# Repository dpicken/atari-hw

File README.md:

# atari-hw

Atari 8-bit hardware projects.

- [Small Form Factor (SFF) Atari 8-bit compatible system](/doc/sbc.md)

- [USB Keyboard Controller for Atari XL/XE computers](/doc/keyboard-usb-qtpy.md)

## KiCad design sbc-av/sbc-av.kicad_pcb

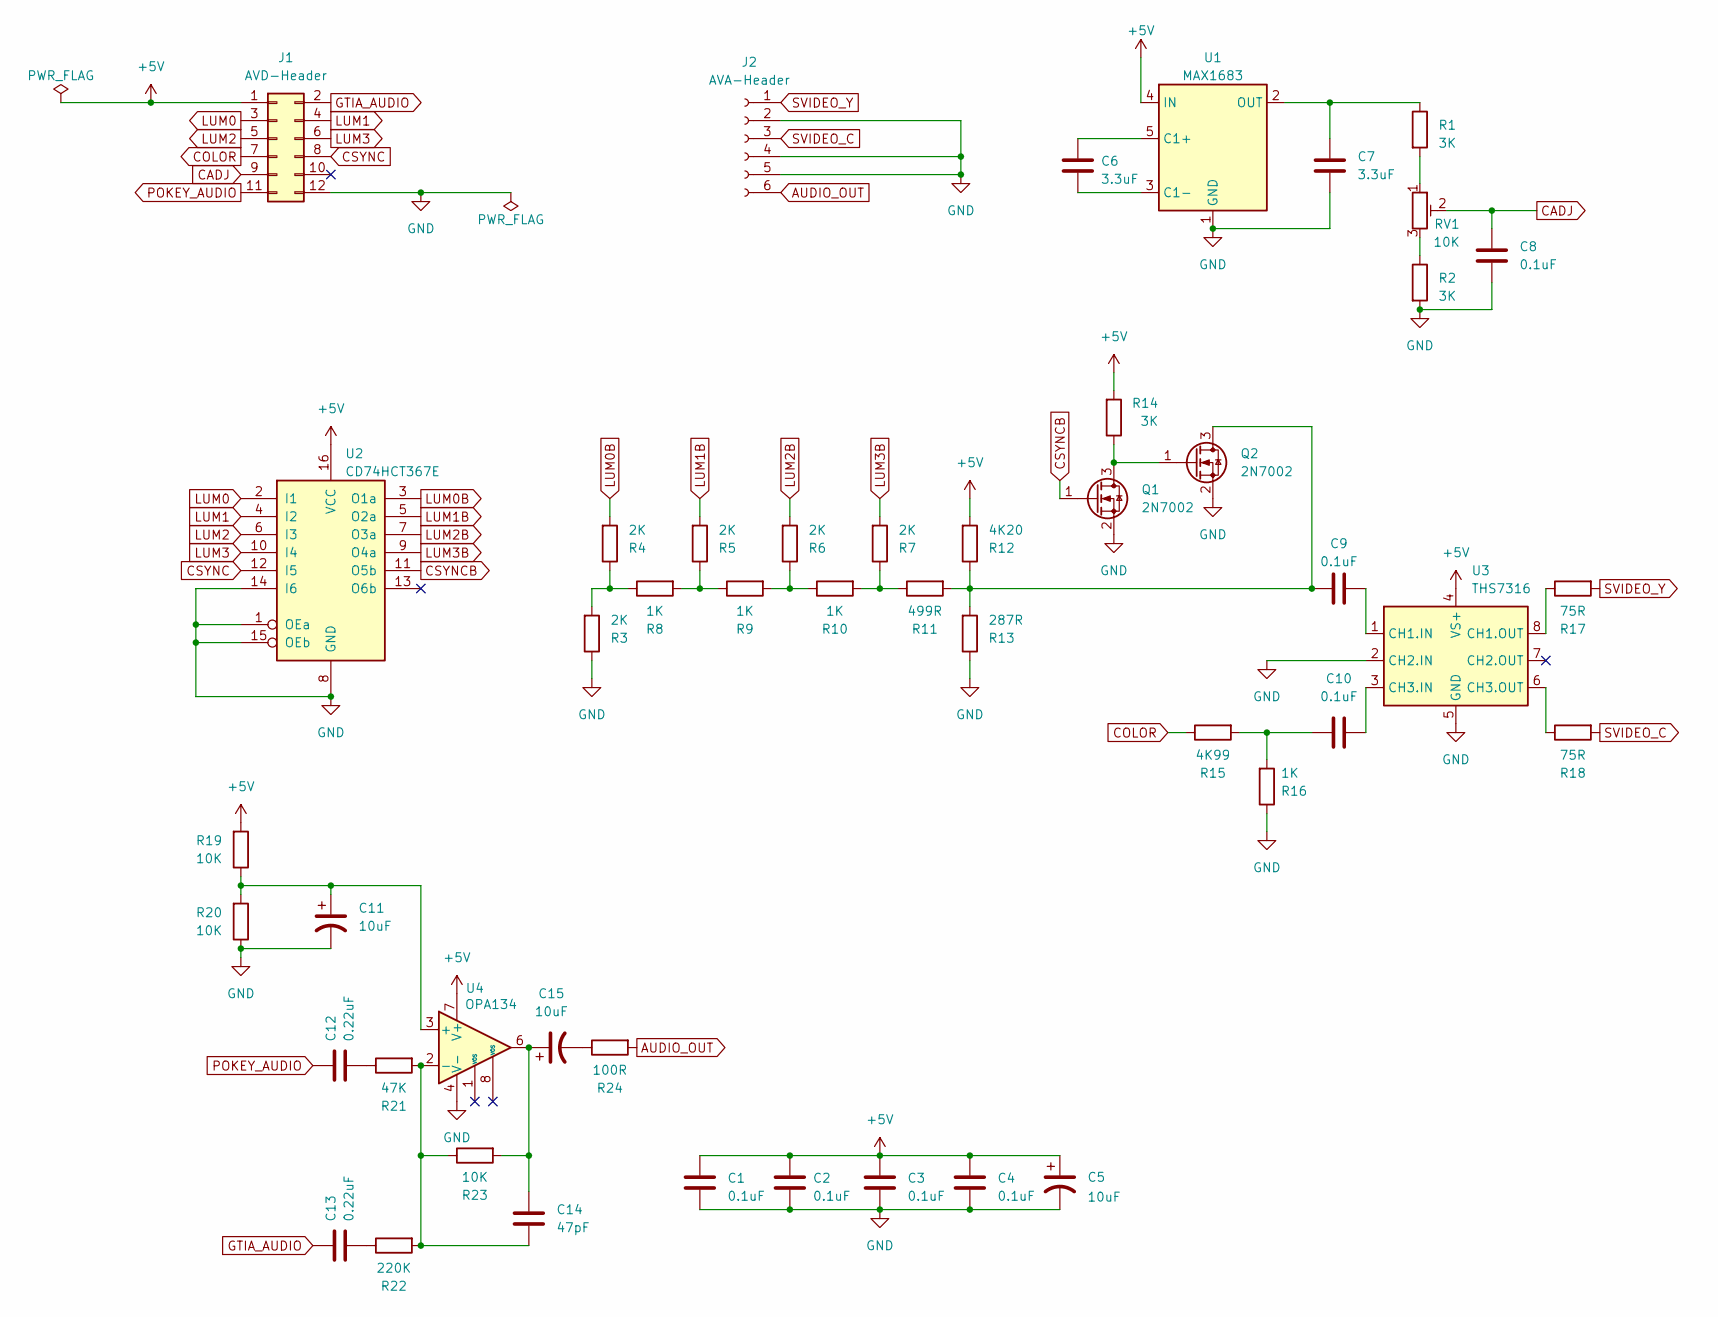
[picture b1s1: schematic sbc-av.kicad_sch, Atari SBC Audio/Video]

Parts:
C1, C2, C3, C4, C8, C9, C10: 0.1uF; C_0805_2012Metric_Pad1.18x1.45mm_HandSolder
C5, C11: 10uF; CP_EIA-2012-15_AVX-P_HandSolder
C6, C7: 3.3uF; C_0805_2012Metric_Pad1.18x1.45mm_HandSolder
C12, C13: 0.22uF; C_1206_3216Metric_Pad1.33x1.80mm_HandSolder
C14: 47pF; C_0805_2012Metric_Pad1.18x1.45mm_HandSolder
C15: 10uF; CP_EIA-3216-18_Kemet-A_HandSolder
J1: AVD-Header; PinHeader_2x06_P2.54mm_Vertical
J2: AVA-Header; PinHeader_1x06_P2.54mm_Vertical
Q1, Q2: 2N7002; SOT-23
R1, R2, R14: 3K; R_0805_2012Metric_Pad1.20x1.40mm_HandSolder
R3, R4, R5, R6, R7: 2K; R_0805_2012Metric_Pad1.20x1.40mm_HandSolder
R8, R9, R10, R16: 1K; R_0805_2012Metric_Pad1.20x1.40mm_HandSolder
R11: 499R; R_0805_2012Metric_Pad1.20x1.40mm_HandSolder
R12: 4K20; R_0805_2012Metric_Pad1.20x1.40mm_HandSolder
R13: 287R; R_0805_2012Metric_Pad1.20x1.40mm_HandSolder
R15: 4K99; R_0805_2012Metric_Pad1.20x1.40mm_HandSolder
R17, R18: 75R; R_0805_2012Metric_Pad1.20x1.40mm_HandSolder
R19, R20, R23: 10K; R_0805_2012Metric_Pad1.20x1.40mm_HandSolder
R21: 47K; R_0805_2012Metric_Pad1.20x1.40mm_HandSolder
R22: 220K; R_0805_2012Metric_Pad1.20x1.40mm_HandSolder
R24: 100R; R_0805_2012Metric_Pad1.20x1.40mm_HandSolder
RV1: 10K; Potentiometer_Bourns_3314G_Vertical
U1: MAX1683; SOT-23-5
U2: CD74HCT367E; SOIC-16_3.9x9.9mm_P1.27mm
U3: THS7316; SOIC-8_3.9x4.9mm_P1.27mm
U4: OPA134; SOIC-8_3.9x4.9mm_P1.27mm

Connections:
+5V: C1.1, C2.1, C3.1, C4.1, C5.1, J1.1, R12.2, R14.2, R19.2, U1.4 (IN), U2.16 (VCC), U3.4 (VS+), U4.7 (V+)
AUDIO_OUT: J2.6, R24.2
CADJ: C8.1, J1.9, RV1.2
COLOR: J1.7, R15.1
CSYNC: J1.8, U2.12 (I5)
CSYNCB: Q1.1 (G), U2.11 (O5b)
GND: C1.2, C2.2, C3.2, C4.2, C5.2, C7.2, C8.2, C11.2, J1.12, J2.2, J2.4, J2.5, Q1.2 (S), Q2.2 (S), R2.2, R3.1, R13.1, R16.1, R20.1, U1.1 (GND), U2.1 (OEa), U2.8 (GND), U2.14 (I6), U2.15 (OEb), U3.2 (CH2.IN), U3.5 (GND), U4.4 (V-)
GTIA_AUDIO: C13.1, J1.2
LUM0: J1.3, U2.2 (I1)
LUM0B: R4.2, U2.3 (O1a)
LUM1: J1.4, U2.4 (I2)
LUM1B: R5.2, U2.5 (O2a)
LUM2: J1.5, U2.6 (I3)
LUM2B: R6.2, U2.7 (O3a)
LUM3: J1.6, U2.10 (I4)
LUM3B: R7.2, U2.9 (O4a)
unnamed: C10.1, R15.2, R16.2
unnamed: C12.2, R21.1
unnamed: C13.2, R22.1
unnamed: C14.2, C15.1, R23.2, U4.6
unnamed: C15.2, R24.1
unnamed: Q1.3 (D), Q2.1 (G), R14.1
unnamed: C9.1, Q2.3 (D), R11.2, R12.1, R13.2
unnamed: R1.2, RV1.1
unnamed: R2.1, RV1.3
unnamed: R3.2, R4.1, R8.1
unnamed: R5.1, R8.2, R9.1
unnamed: R6.1, R9.2, R10.1
unnamed: R7.1, R10.2, R11.1
unnamed: C6.1, U1.5 (C1+)
unnamed: C6.2, U1.3 (C1-)
unnamed: C7.1, R1.1, U1.2 (OUT)
unnamed: C9.2, U3.1 (CH1.IN)
unnamed: R17.1, U3.8 (CH1.OUT)
unnamed: C10.2, U3.3 (CH3.IN)
unnamed: R18.1, U3.6 (CH3.OUT)
unnamed: C11.1, R19.1, R20.2, U4.3 (+)
unnamed: C14.1, R21.2, R22.2, R23.1, U4.2 (-)
POKEY_AUDIO: C12.1, J1.11
SVIDEO_C: J2.3, R18.2
SVIDEO_Y: J2.1, R17.2

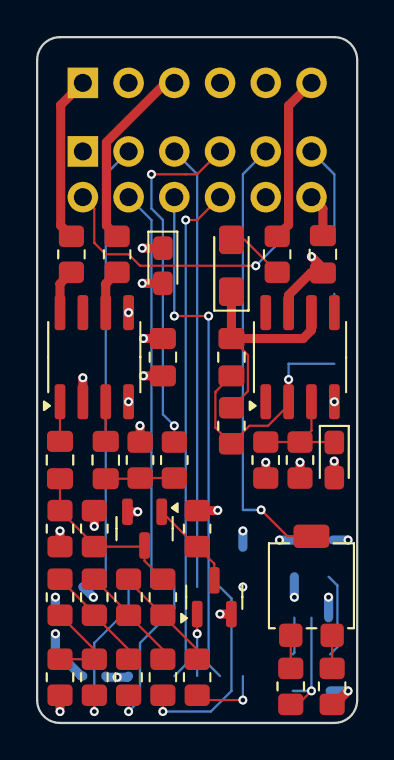
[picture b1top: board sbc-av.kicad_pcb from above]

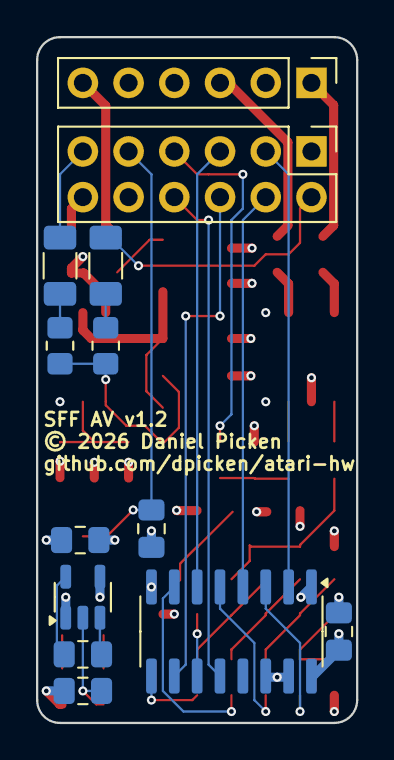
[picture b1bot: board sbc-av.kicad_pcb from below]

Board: 4 copper layers, 17.8 x 38.1 mm, 48 parts (13 on the bottom side), 41 nets.

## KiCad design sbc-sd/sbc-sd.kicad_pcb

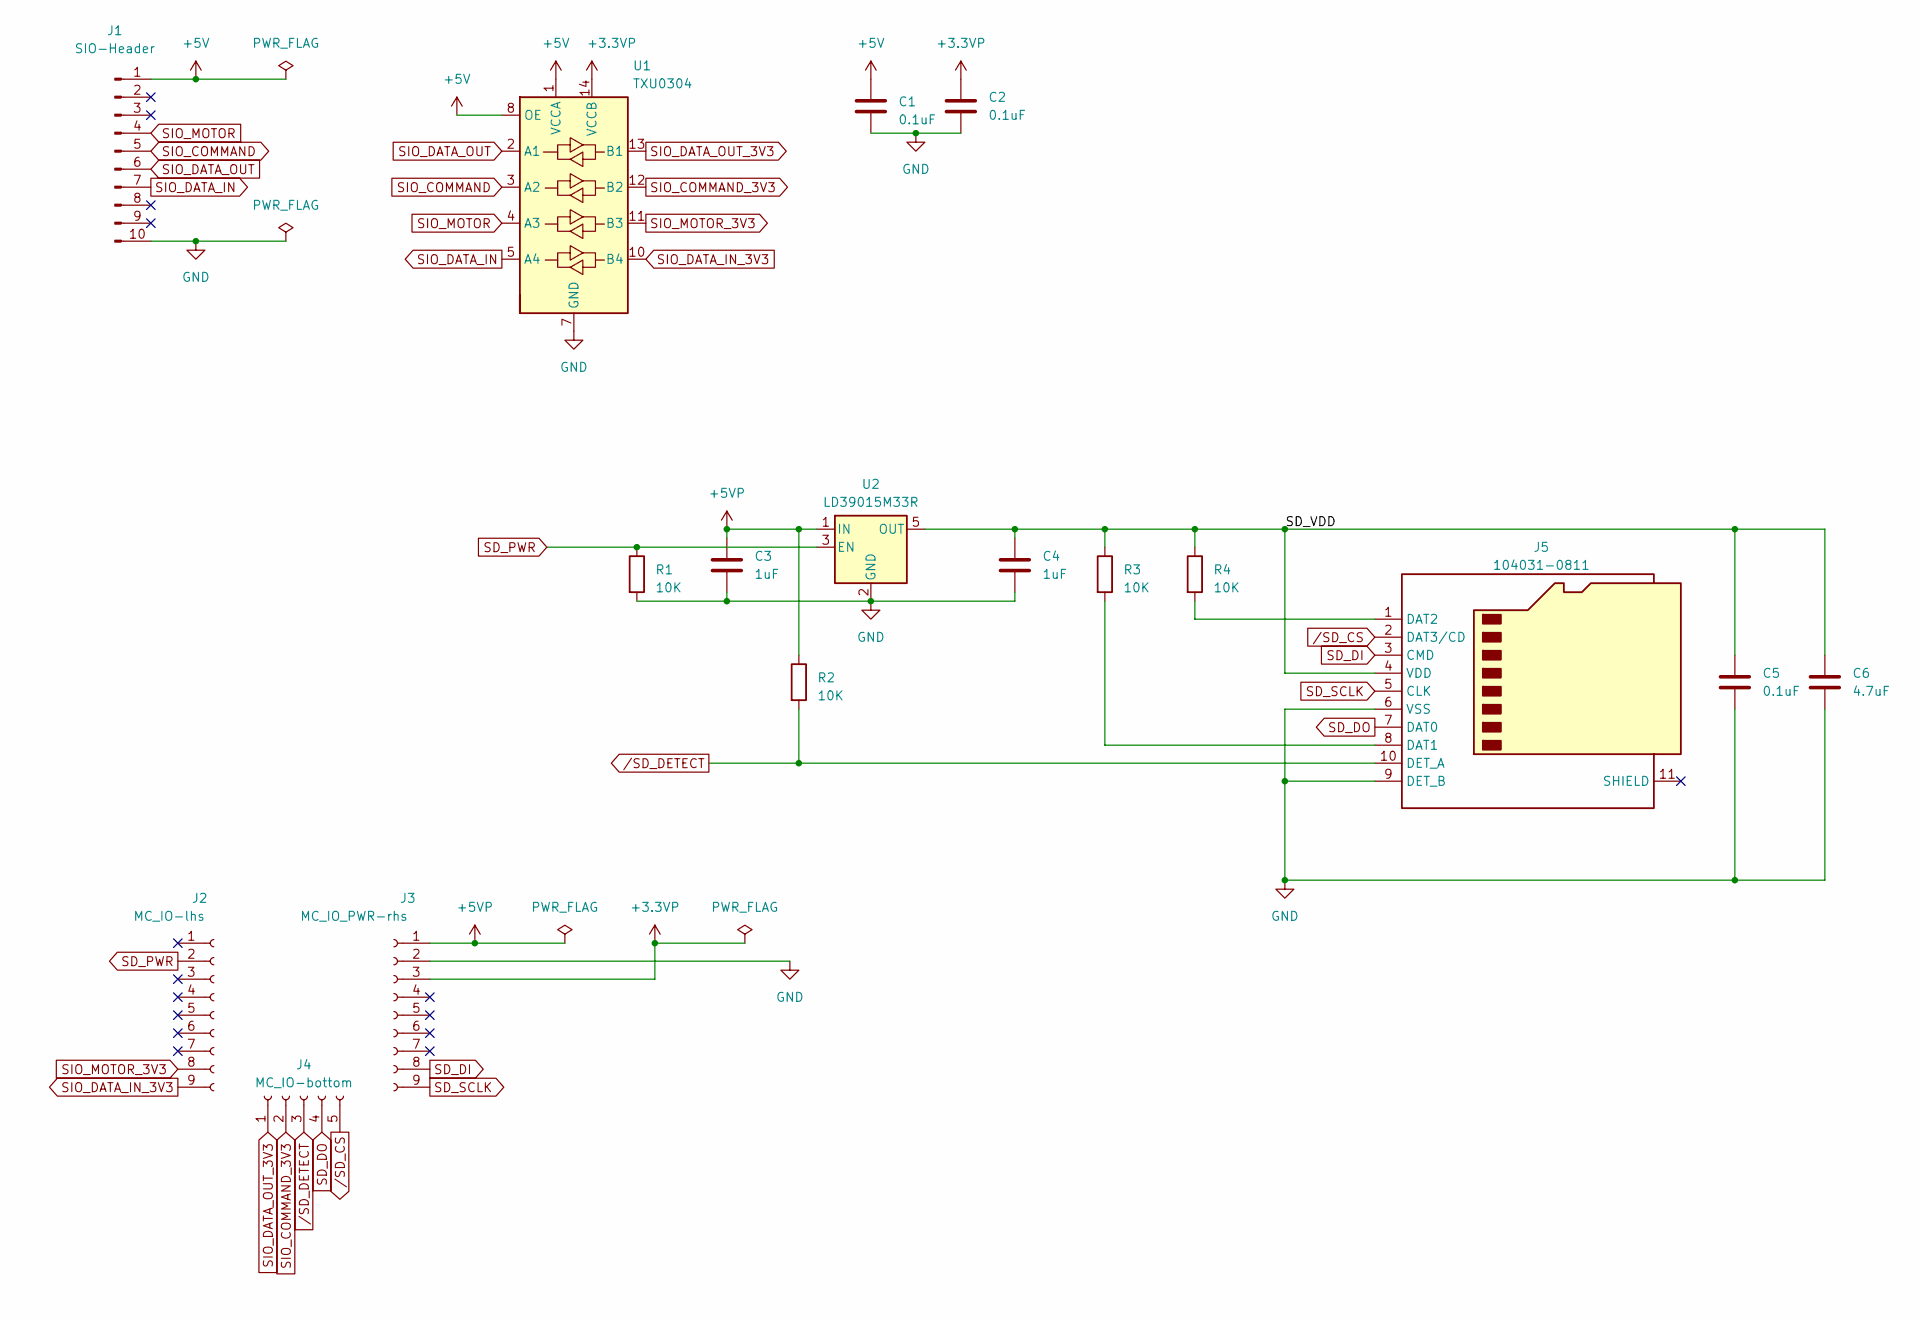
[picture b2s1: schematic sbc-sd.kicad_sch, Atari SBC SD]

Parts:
C1, C2, C5: 0.1uF; C_0805_2012Metric_Pad1.18x1.45mm_HandSolder
C3, C4: 1uF; C_0805_2012Metric_Pad1.18x1.45mm_HandSolder
C6: 4.7uF; C_0805_2012Metric_Pad1.18x1.45mm_HandSolder
J1: SIO-Header; PinHeader_1x10_P2.54mm_Vertical
J2: MC_IO-lhs; PinHeader_1x09_P2.54mm_Vertical
J3: MC_IO_PWR-rhs; PinHeader_1x09_P2.54mm_Vertical
J4: MC_IO-bottom; PinHeader_1x05_P2.54mm_Vertical
J5: 104031-0811; microSD_HC_Molex_104031-0811
R1, R2, R3, R4: 10K; R_0805_2012Metric_Pad1.20x1.40mm_HandSolder
U1: TXU0304; TSSOP-14_4.4x5mm_P0.65mm
U2: LD39015M33R; SOT-23-5

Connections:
+3.3VP: C2.1, J3.3, U1.14 (VCCB)
+5V: C1.1, J1.1, U1.1 (VCCA), U1.8 (OE)
+5VP: C3.1, J3.1, R2.1, U2.1 (IN)
/SD_VDD: C4.1, C5.1, C6.1, J5.4 (VDD), R3.1, R4.1, U2.5 (OUT)
GND: C1.2, C2.2, C3.2, C4.2, C5.2, C6.2, J1.10, J3.2, J5.6 (VSS), J5.9 (DET_B), R1.2, U1.7 (GND), U2.2 (GND)
unnamed: J5.8 (DAT1), R3.2
unnamed: J5.1 (DAT2), R4.2
SD_DI: J3.8, J5.3 (CMD)
SD_DO: J4.4, J5.7 (DAT0)
SD_PWR: J2.2, R1.1, U2.3 (EN)
SD_SCLK: J3.9, J5.5 (CLK)
SIO_COMMAND: J1.5, U1.3 (A2)
SIO_COMMAND_3V3: J4.2, U1.12 (B2)
SIO_DATA_IN: J1.7, U1.5 (A4)
SIO_DATA_IN_3V3: J2.9, U1.10 (B4)
SIO_DATA_OUT: J1.6, U1.2 (A1)
SIO_DATA_OUT_3V3: J4.1, U1.13 (B1)
SIO_MOTOR: J1.4, U1.4 (A3)
SIO_MOTOR_3V3: J2.8, U1.11 (B3)
/SD_CS: J4.5, J5.2 (DAT3/CD)
/SD_DETECT: J4.3, J5.10 (DET_A), R2.2

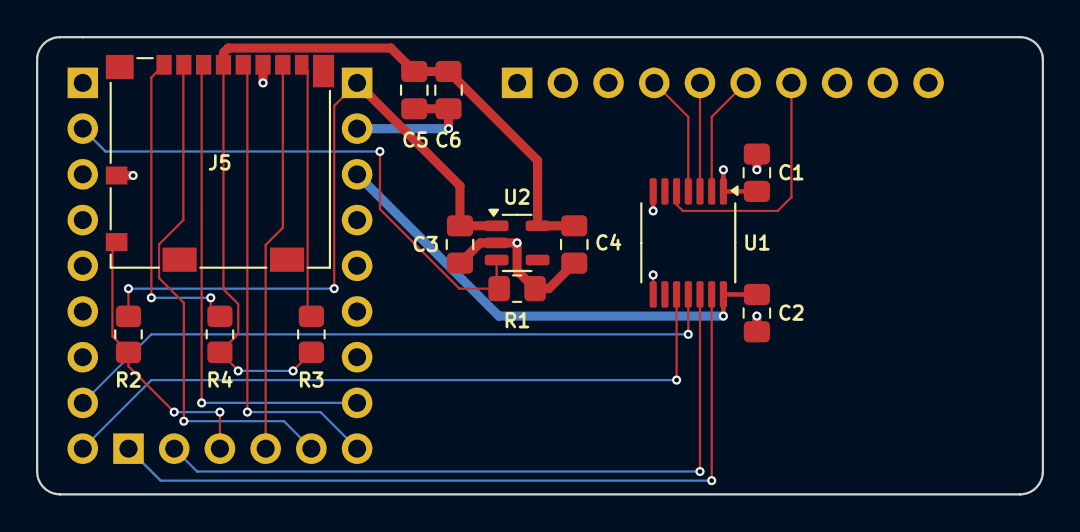
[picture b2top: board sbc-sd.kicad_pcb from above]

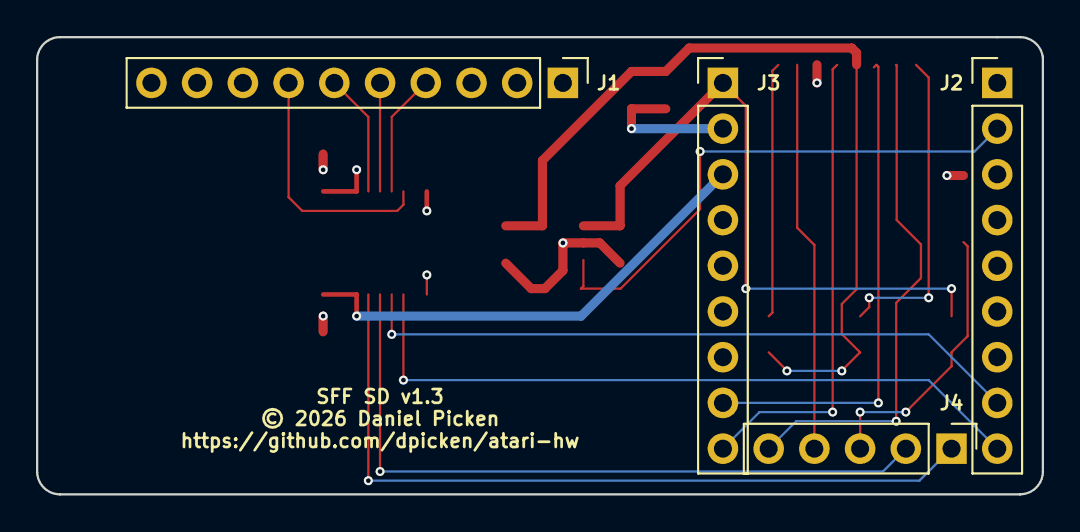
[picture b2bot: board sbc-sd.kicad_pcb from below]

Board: 4 copper layers, 55.9 x 25.4 mm, 17 parts (4 on the bottom side), 21 nets.

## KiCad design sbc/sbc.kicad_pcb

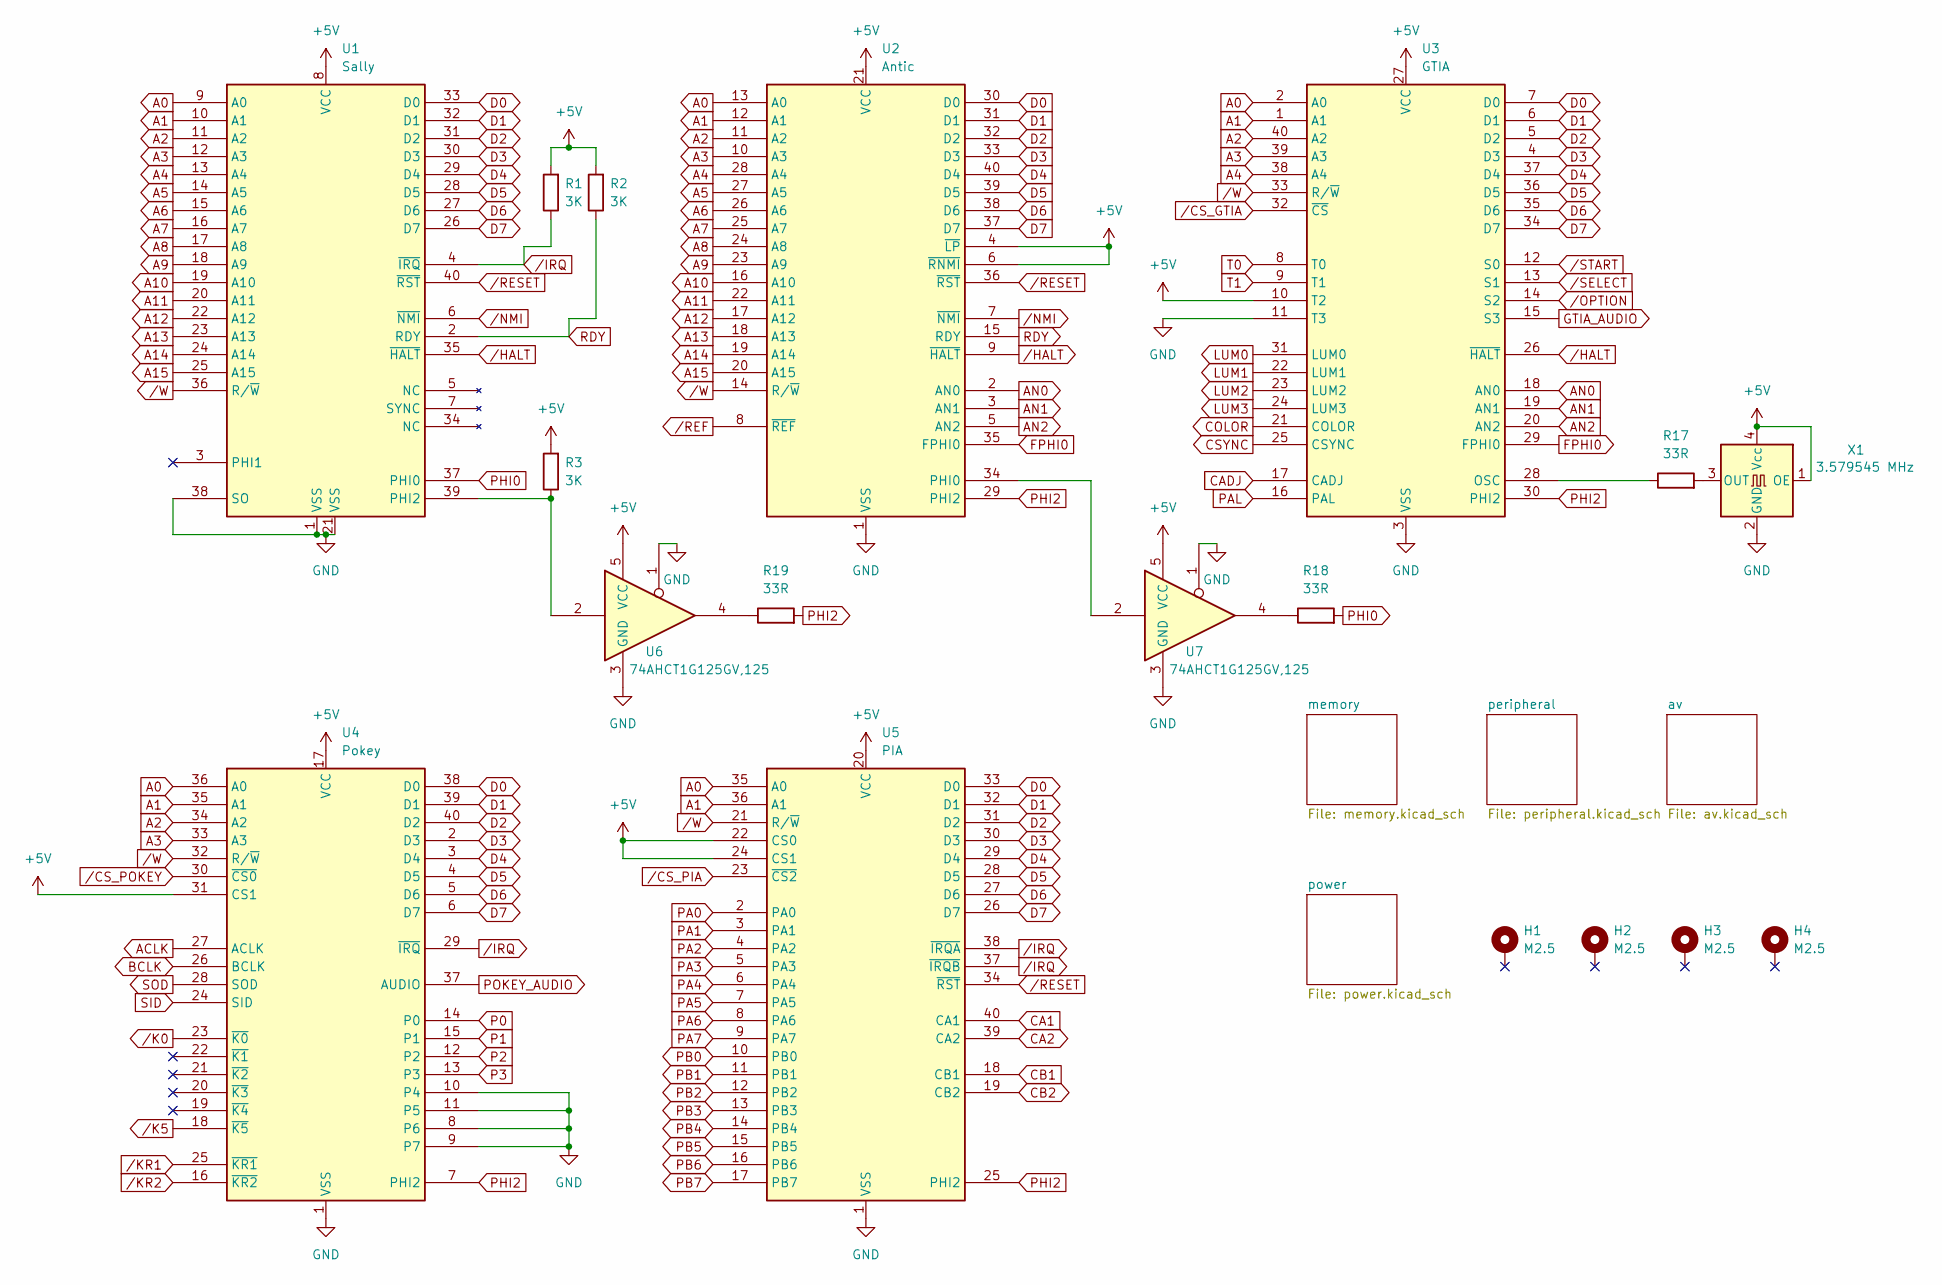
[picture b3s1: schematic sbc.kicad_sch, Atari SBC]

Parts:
H1, H2, H3, H4: M2.5; MountingHole_2.7mm_M2.5_Pad
R1, R2, R3: 3K; R_0805_2012Metric_Pad1.20x1.40mm_HandSolder
R17, R18, R19: 33R; R_0805_2012Metric_Pad1.20x1.40mm_HandSolder
U1: Sally; DIP-40_W15.24mm_Socket
U2: Antic; DIP-40_W15.24mm_Socket
U3: GTIA; DIP-40_W15.24mm_Socket
U4: Pokey; DIP-40_W15.24mm_Socket
U5: PIA; DIP-40_W15.24mm_Socket
U6, U7: 74AHCT1G125GV,125; SOT-23-5_HandSoldering
X1: 3.579545 MHz; Oscillator_SMD_SeikoEpson_SG8002CA-4Pin_7.0x5.0mm

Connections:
+5V: R1.2, R2.2, R3.2, U1.8 (VCC), U2.4 (~LP), U2.6 (~RNMI), U2.21 (VCC), U3.10 (T2), U3.27 (VCC), U4.17 (VCC), U4.31 (CS1), U5.20 (VCC), U5.22 (CS0), U5.24 (CS1), U6.5 (VCC), U7.5 (VCC), X1.1 (OE), X1.4 (Vcc); also elsewhere on the board
A0: U1.9 (A0), U2.13 (A0), U3.2 (A0), U4.36 (A0), U5.35 (A0); also elsewhere on the board
A1: U1.10 (A1), U2.12 (A1), U3.1 (A1), U4.35 (A1), U5.36 (A1); also elsewhere on the board
A2: U1.11 (A2), U2.11 (A2), U3.40 (A2), U4.34 (A2); also elsewhere on the board
A3: U1.12 (A3), U2.10 (A3), U3.39 (A3), U4.33 (A3); also elsewhere on the board
A4: U1.13 (A4), U2.28 (A4), U3.38 (A4); also elsewhere on the board
A5: U1.14 (A5), U2.27 (A5); also elsewhere on the board
A6: U1.15 (A6), U2.26 (A6); also elsewhere on the board
A7: U1.16 (A7), U2.25 (A7); also elsewhere on the board
A8: U1.17 (A8), U2.24 (A8); also elsewhere on the board
A9: U1.18 (A9), U2.23 (A9); also elsewhere on the board
A10: U1.19 (A10), U2.16 (A10); also elsewhere on the board
A11: U1.20 (A11), U2.22 (A11); also elsewhere on the board
A12: U1.22 (A12), U2.17 (A12); also elsewhere on the board
A13: U1.23 (A13), U2.18 (A13); also elsewhere on the board
A14: U1.24 (A14), U2.19 (A14); also elsewhere on the board
A15: U1.25 (A15), U2.20 (A15); also elsewhere on the board
ACLK: U4.27 (ACLK); also elsewhere on the board
AN0: U2.2 (AN0), U3.18 (AN0)
AN1: U2.3 (AN1), U3.19 (AN1)
AN2: U2.5 (AN2), U3.20 (AN2)
BCLK: U4.26 (BCLK); also elsewhere on the board
CA1: U5.40 (CA1); also elsewhere on the board
CA2: U5.39 (CA2); also elsewhere on the board
CADJ: U3.17 (CADJ); also elsewhere on the board
CB1: U5.18 (CB1); also elsewhere on the board
CB2: U5.19 (CB2); also elsewhere on the board
COLOR: U3.21 (COLOR); also elsewhere on the board
CSYNC: U3.25 (CSYNC); also elsewhere on the board
D0: U1.33 (D0), U2.30 (D0), U3.7 (D0), U4.38 (D0), U5.33 (D0); also elsewhere on the board
D1: U1.32 (D1), U2.31 (D1), U3.6 (D1), U4.39 (D1), U5.32 (D1); also elsewhere on the board
D2: U1.31 (D2), U2.32 (D2), U3.5 (D2), U4.40 (D2), U5.31 (D2); also elsewhere on the board
D3: U1.30 (D3), U2.33 (D3), U3.4 (D3), U4.2 (D3), U5.30 (D3); also elsewhere on the board
D4: U1.29 (D4), U2.40 (D4), U3.37 (D4), U4.3 (D4), U5.29 (D4); also elsewhere on the board
D5: U1.28 (D5), U2.39 (D5), U3.36 (D5), U4.4 (D5), U5.28 (D5); also elsewhere on the board
D6: U1.27 (D6), U2.38 (D6), U3.35 (D6), U4.5 (D6), U5.27 (D6); also elsewhere on the board
D7: U1.26 (D7), U2.37 (D7), U3.34 (D7), U4.6 (D7), U5.26 (D7); also elsewhere on the board
FPHI0: U2.35 (FPHI0), U3.29 (FPHI0)
GND: U1.1 (VSS), U1.21 (VSS), U1.38 (SO), U2.1 (VSS), U3.3 (VSS), U3.11 (T3), U4.1 (VSS), U4.8 (P6), U4.9 (P7), U4.10 (P4), U4.11 (P5), U5.1 (VSS), U6.1, U6.3 (GND), U7.1, U7.3 (GND), X1.2 (GND); also elsewhere on the board
GTIA_AUDIO: U3.15 (S3); also elsewhere on the board
LUM0: U3.31 (LUM0); also elsewhere on the board
LUM1: U3.22 (LUM1); also elsewhere on the board
LUM2: U3.23 (LUM2); also elsewhere on the board
LUM3: U3.24 (LUM3); also elsewhere on the board
unnamed: R18.1, U7.4
unnamed: R19.1, U6.4
unnamed: R3.1, U1.39 (PHI2), U6.2
unnamed: U2.34 (PHI0), U7.2
unnamed: R17.1, U3.28 (OSC)
unnamed: R17.2, X1.3 (OUT)
P0: U4.14 (P0); also elsewhere on the board
P1: U4.15 (P1); also elsewhere on the board
P2: U4.12 (P2); also elsewhere on the board
P3: U4.13 (P3); also elsewhere on the board
PA0: U5.2 (PA0); also elsewhere on the board
PA1: U5.3 (PA1); also elsewhere on the board
PA2: U5.4 (PA2); also elsewhere on the board
PA3: U5.5 (PA3); also elsewhere on the board
PA4: U5.6 (PA4); also elsewhere on the board
PA5: U5.7 (PA5); also elsewhere on the board
PA6: U5.8 (PA6); also elsewhere on the board
PA7: U5.9 (PA7); also elsewhere on the board
PAL: U3.16 (PAL); also elsewhere on the board
PB0: U5.10 (PB0); also elsewhere on the board
PB1: U5.11 (PB1); also elsewhere on the board
PB2: U5.12 (PB2); also elsewhere on the board
PB3: U5.13 (PB3); also elsewhere on the board
PB4: U5.14 (PB4); also elsewhere on the board
PB5: U5.15 (PB5); also elsewhere on the board
PB6: U5.16 (PB6); also elsewhere on the board
PB7: U5.17 (PB7); also elsewhere on the board
PHI0: R18.2, U1.37 (PHI0); also elsewhere on the board
PHI2: R19.2, U2.29 (PHI2), U3.30 (PHI2), U4.7 (PHI2), U5.25 (PHI2); also elsewhere on the board
POKEY_AUDIO: U4.37 (AUDIO); also elsewhere on the board
RDY: R2.1, U1.2 (RDY), U2.15 (RDY)
SID: U4.24 (SID); also elsewhere on the board
SOD: U4.28 (SOD); also elsewhere on the board
T0: U3.8 (T0); also elsewhere on the board
T1: U3.9 (T1); also elsewhere on the board
/CS_GTIA: U3.32 (~CS); also elsewhere on the board
/CS_PIA: U5.23 (~CS2); also elsewhere on the board
/CS_POKEY: U4.30 (~CS0); also elsewhere on the board
/HALT: U1.35 (~HALT), U2.9 (~HALT), U3.26 (~HALT); also elsewhere on the board
/IRQ: R1.1, U1.4 (~IRQ), U4.29 (~IRQ), U5.37 (~IRQB), U5.38 (~IRQA)
/K0: U4.23 (~K0); also elsewhere on the board
/K5: U4.18 (~K5); also elsewhere on the board
/KR1: U4.25 (~KR1); also elsewhere on the board
/KR2: U4.16 (~KR2); also elsewhere on the board
/NMI: U1.6 (~NMI), U2.7 (~NMI)
/OPTION: U3.14 (S2); also elsewhere on the board
/REF: U2.8 (~REF); also elsewhere on the board
/RESET: U1.40 (~RST), U2.36 (~RST), U5.34 (~RST); also elsewhere on the board
/SELECT: U3.13 (S1); also elsewhere on the board
/START: U3.12 (S0); also elsewhere on the board
/W: U1.36 (R/~W), U2.14 (R/~W), U3.33 (R/~W), U4.32 (R/~W), U5.21 (R/~W); also elsewhere on the board

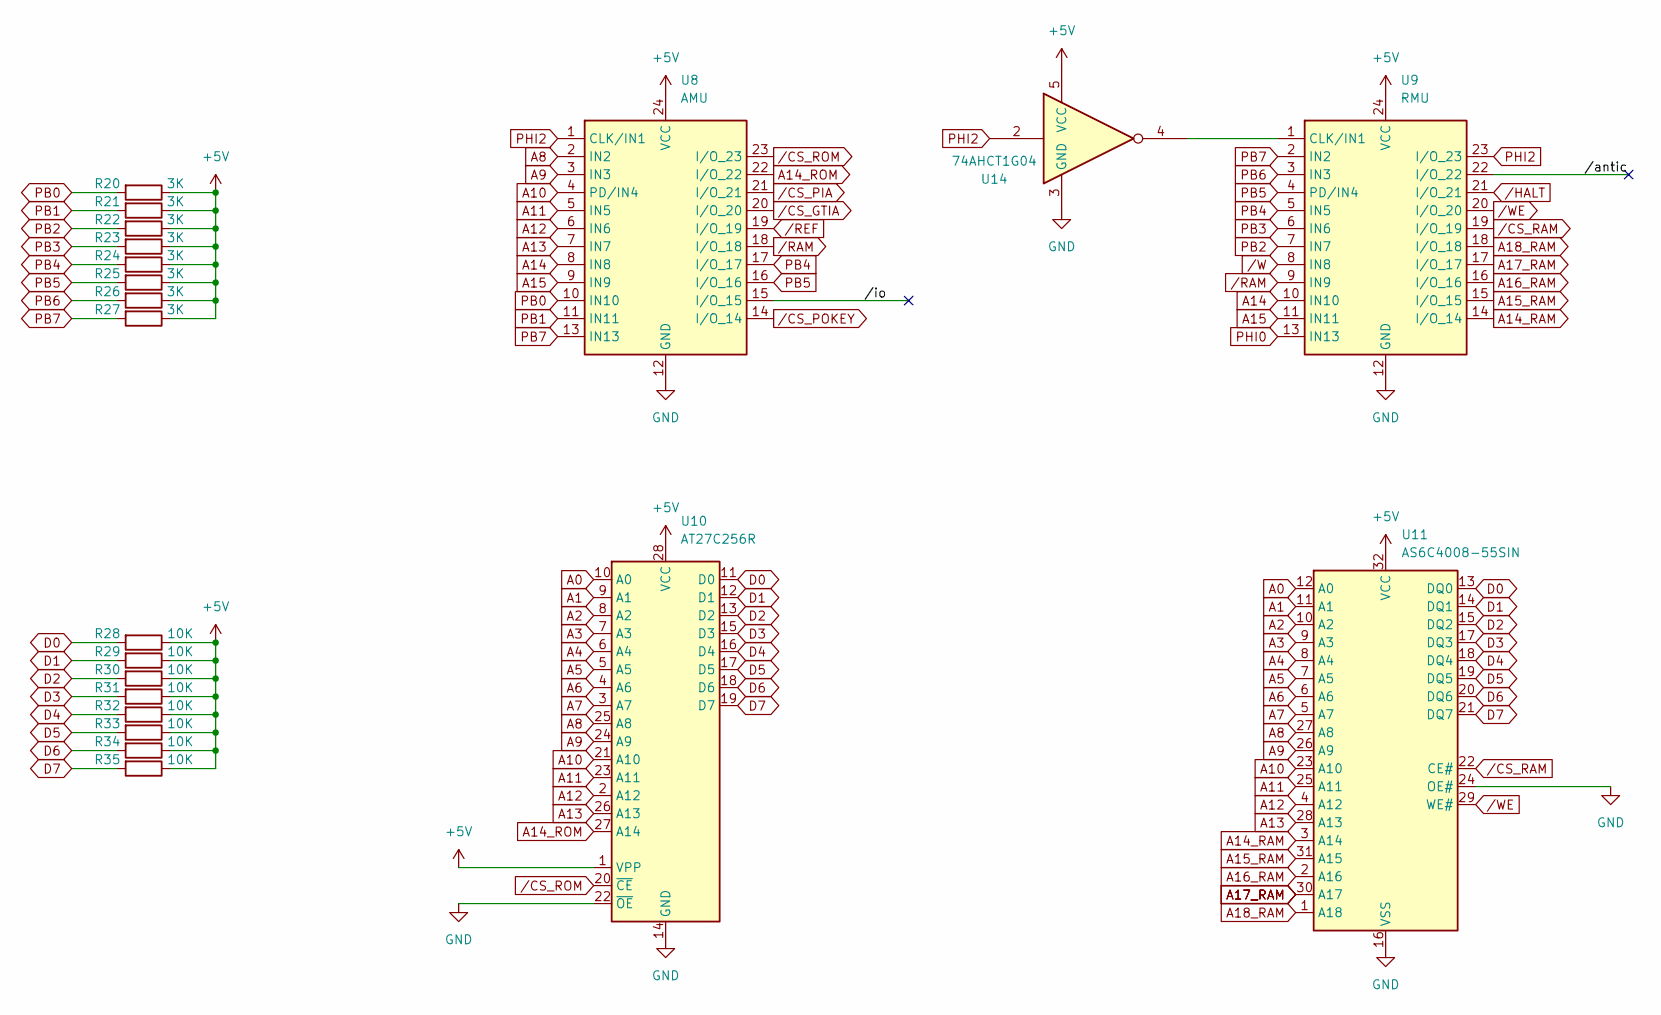
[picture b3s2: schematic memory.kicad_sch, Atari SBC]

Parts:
R20, R21, R22, R23, R24, R25, R26, R27: 3K; R_0805_2012Metric_Pad1.20x1.40mm_HandSolder
R28, R29, R30, R31, R32, R33, R34, R35: 10K; R_0805_2012Metric_Pad1.20x1.40mm_HandSolder
U8: AMU; DIP-24_W7.62mm_Socket
U9: RMU; DIP-24_W7.62mm_Socket
U10: AT27C256R; DIP-28_W15.24mm_Socket
U11: AS6C4008-55SIN; SOP-32_11.305x20.495mm_P1.27mm
U14: 74AHCT1G04; SOT-23-5_HandSoldering

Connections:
+5V: R20.1, R21.1, R22.1, R23.1, R24.1, R25.1, R26.1, R27.1, R28.1, R29.1, R30.1, R31.1, R32.1, R33.1, R34.1, R35.1, U8.24 (VCC), U9.24 (VCC), U10.1 (VPP), U10.28 (VCC), U11.32 (VCC), U14.5 (VCC); also elsewhere on the board
/memory//antic: U9.22 (I/O_22)
/memory//io: U8.15 (I/O_15)
A0: U10.10 (A0), U11.12 (A0); also elsewhere on the board
A1: U10.9 (A1), U11.11 (A1); also elsewhere on the board
A2: U10.8 (A2), U11.10 (A2); also elsewhere on the board
A3: U10.7 (A3), U11.9 (A3); also elsewhere on the board
A4: U10.6 (A4), U11.8 (A4); also elsewhere on the board
A5: U10.5 (A5), U11.7 (A5); also elsewhere on the board
A6: U10.4 (A6), U11.6 (A6); also elsewhere on the board
A7: U10.3 (A7), U11.5 (A7); also elsewhere on the board
A8: U8.2 (IN2), U10.25 (A8), U11.27 (A8); also elsewhere on the board
A9: U8.3 (IN3), U10.24 (A9), U11.26 (A9); also elsewhere on the board
A10: U8.4 (PD/IN4), U10.21 (A10), U11.23 (A10); also elsewhere on the board
A11: U8.5 (IN5), U10.23 (A11), U11.25 (A11); also elsewhere on the board
A12: U8.6 (IN6), U10.2 (A12), U11.4 (A12); also elsewhere on the board
A13: U8.7 (IN7), U10.26 (A13), U11.28 (A13); also elsewhere on the board
A14: U8.8 (IN8), U9.10 (IN10); also elsewhere on the board
A14_RAM: U9.14 (I/O_14), U11.3 (A14)
A14_ROM: U8.22 (I/O_22), U10.27 (A14)
A15: U8.9 (IN9), U9.11 (IN11); also elsewhere on the board
A15_RAM: U9.15 (I/O_15), U11.31 (A15)
A16_RAM: U9.16 (I/O_16), U11.2 (A16)
A17_RAM: U9.17 (I/O_17), U11.30 (A17)
A18_RAM: U9.18 (I/O_18), U11.1 (A18)
D0: R28.2, U10.11 (D0), U11.13 (DQ0); also elsewhere on the board
D1: R29.2, U10.12 (D1), U11.14 (DQ1); also elsewhere on the board
D2: R30.2, U10.13 (D2), U11.15 (DQ2); also elsewhere on the board
D3: R31.2, U10.15 (D3), U11.17 (DQ3); also elsewhere on the board
D4: R32.2, U10.16 (D4), U11.18 (DQ4); also elsewhere on the board
D5: R33.2, U10.17 (D5), U11.19 (DQ5); also elsewhere on the board
D6: R34.2, U10.18 (D6), U11.20 (DQ6); also elsewhere on the board
D7: R35.2, U10.19 (D7), U11.21 (DQ7); also elsewhere on the board
GND: U8.12 (GND), U9.12 (GND), U10.14 (GND), U10.22 (~OE), U11.16 (VSS), U11.24 (OE#), U14.3 (GND); also elsewhere on the board
unnamed: U9.1 (CLK/IN1), U14.4
PB0: R20.2, U8.10 (IN10); also elsewhere on the board
PB1: R21.2, U8.11 (IN11); also elsewhere on the board
PB2: R22.2, U9.7 (IN7); also elsewhere on the board
PB3: R23.2, U9.6 (IN6); also elsewhere on the board
PB4: R24.2, U8.17 (I/O_17), U9.5 (IN5); also elsewhere on the board
PB5: R25.2, U8.16 (I/O_16), U9.4 (PD/IN4); also elsewhere on the board
PB6: R26.2, U9.3 (IN3); also elsewhere on the board
PB7: R27.2, U8.13 (IN13), U9.2 (IN2); also elsewhere on the board
PHI0: U9.13 (IN13); also elsewhere on the board
PHI2: U8.1 (CLK/IN1), U9.23 (I/O_23), U14.2; also elsewhere on the board
/CS_GTIA: U8.20 (I/O_20); also elsewhere on the board
/CS_PIA: U8.21 (I/O_21); also elsewhere on the board
/CS_POKEY: U8.14 (I/O_14); also elsewhere on the board
/CS_RAM: U9.19 (I/O_19), U11.22 (CE#)
/CS_ROM: U8.23 (I/O_23), U10.20 (~CE)
/HALT: U9.21 (I/O_21); also elsewhere on the board
/RAM: U8.18 (I/O_18), U9.9 (IN9)
/REF: U8.19 (I/O_19); also elsewhere on the board
/W: U9.8 (IN8); also elsewhere on the board
/WE: U9.20 (I/O_20), U11.29 (WE#)

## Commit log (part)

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2022-10-26 Atari LSI
    Add symbols for Sally, Antic, GTIA, Pokey and PIA.
2022-10-26 firmware/atari-fw_qtpy.uf2:
2022-10-26 README.md:
2022-10-26 Experimental pokey USB keyboard controller
2022-10-26 Remove the experimental pokey USB keyboard controller
2022-10-26 Pokey and GTIA interposers with remote USB keyboard controller
2022-11-19 kicad/symbols/Logic_Programmable.kicad_sym:
2022-11-19 sbc-memory-map.txt:
2022-11-29 WIP: SBC
2023-01-31 Pokey and GTIA interposers with SAMD-based USB keyboard controller
2023-01-31 Remove the SAMD-based USB keyboard controller
    Microchip want ~$200 for a SAMD programmer. RP2040 has a cheaper/simpler/better ecosystem.
2023-01-31 RP2040-based USB keyboard controller
2023-01-31 KiCad symbols and footprints to support an 8-bit Atari SBC
2023-04-09 8-bit Atari SBC
2023-09-02 SBC v1.1
    PCB fixes/changes:
    - Permanently power voltage translators
    - Conservatively specified a slower SRAM (the previous/faster SRAM does actually work fine)
    - RMU: Speculatively provided unbuffered PHI0 input and OE output (not actually needed)
    - Add pullups to open drain GTIA outputs
    - Plot selected values on silk screen
2023-10-17 SBC v1.2
    SBC fixes/changes:
    - S-Video:
    - Fix S-Video footprint (Y and C swapped, and GNDs swapped) and adapt schematic to match
    - Wire S-Video grounds to AVA header instead of directly to (digital) GND
    - Audio:
    - Wire Audio-Out ground to AVA header
2023-10-26 SD card adapter v1.2
    - Move SD card connector closer to the edge of the board
    - Pullup SD detect signal to non-switched 5V
    - Eliminate SD DO pullup
    - Move LDO closer to SD
2024-11-09 Refresh microcontroller firmware images
    - add SD card support
    - add support for Pimoroni's Tiny 2350
2024-12-03 Refresh microcontroller firmware images
    - add SD card support
    - improve ATR file compatibility
    - add support for Pimoroni's Tiny 2350
2025-03-05 main -> master link fixes
2025-07-07 Add support for 320K compy and 130XE
2026-01-23 Documentation update and linux build host fixes
2026-02-07 Refresh firmware images
    - add GPT partition support
    - add xex file loading
    - search for !sbc-filer.xex and !sbc-xex-loader.atr on the SD card and builtin devices
    - case-insensitive file name extension matching in the sio file system device
    - exFat fixes (cluster-chain following and deleted directory entry skipping)
2026-04-14 SBC v1.3
    Motherboard updates:
    - KiCad 9 upgrade
    - USB-C power connector
    - Replace EOL resistor packs with discrete SMD resistors
    - Power/enable voltage translators from switched 5V
    - Fix motor signal pullup

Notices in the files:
gtia-interposer/gtia-interposer.kicad_pcb:
© 2022 Daniel Picken
sbc-av/sbc-av.kicad_pcb:
© 2026 Daniel Picken
